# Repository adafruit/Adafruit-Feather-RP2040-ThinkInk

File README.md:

## Adafruit Feather RP2040 ThinkInk with 24-pin E-Paper Display - STEMMA QT PCB

<a href="http://www.adafruit.com/products/5727"><br/>
Click here to purchase one from the Adafruit shop</a>

PCB files for the Adafruit Feather RP2040 ThinkInk with 24-pin E-Paper Display - STEMMA QT. 

Format is EagleCAD schematic and board layout
* https://www.adafruit.com/product/5727

### Description

Easy e-paper and RP2040 finally come to your Feather with this Adafruit RP2040 Feather Think Ink that's designed to make it a breeze to add almost any common e-Ink/e-Paper display. Chances are you've seen one of those new-fangled 'e-readers' like the Kindle or Nook. They have gigantic electronic paper 'static' displays - that means the image stays on the display even when power is completely disconnected. The image is also high contrast and very daylight readable. It really does look just like printed paper!

We've liked these displays for a long time, and we've got Arduino/CircuitPython drivers for tons of the various display chipsets, so wouldn't an e-paper RP2040 Feather make a ton of sense? Luckily for us, just about every small-medium size EInk display made these days has a standard 24-pin connection. This Feather will add all the power supply support circuitry and level shifting so you can attach your favorite display - we've tested it with up to 5.6" sized 7-color ACeP displays.

Since all ePaper displays with the 24-pin interface require you to buffer the layers of data and write them all out at once over SPI, the RP2040 chip is an excellent driver. It has 264K of internal SRAM so even with the largest displays, there's plenty of memory to store all the image data plus run your own code. We also put the display on it's own SPI port so that the Feather's main SPI port can be used for other peripheral devices.

Feather is the development board specification from Adafruit, and like its namesake, it is thin, light, and lets you fly! We designed Feather to be a new standard for portable microcontroller cores. We have other boards in the Feather family, check'em out here.

At the Feather's heart is an RP2040 chip, clocked at 133 MHz and at 3.3V logic, the same one used in the Raspberry Pi Pico. This chip has a whopping MB of onboard QSPI FLASH and 264K of RAM!  There's even room left over for a STEMMA QT connector for plug-and-play of I2C devices.

To make it easy to use for portable projects, we added a connector for any of our 3.7V Lithium polymer batteries and built-in battery charging. You don't need a battery, it will run just fine straight from the USB Type C connector. But, if you do have a battery, you can take it on the go, then plug in the USB to recharge. The Feather will automatically switch over to USB power when it's available. While the RP2040 is not designed for low power usage - you can get down to about 1.5mA of power draw in sleep mode.

Here're some handy specs! You get:

* Measures 2.0" x 0.9" x 0.28" (50.8mm x 22.8mm x 7mm) without headers soldered in
* Light as a (large?) feather - 6.3 grams
* RP2040 32-bit Cortex M0+ dual core running at ~133 MHz @ 3.3V logic and power
* 264 KB RAM
* 8 MB SPI FLASH chip for storing files, images and CircuitPython/MicroPython code storage. No EEPROM
* Tons of GPIO! 21 x GPIO pins with following capabilities:
	* Four 12-bit ADCs (one more than Pico)
	* Two I2C, Two SPI, and two UART peripherals, we label one for the 'main' interface in standard Feather locations
	* 16 x PWM outputs - for servos, LEDs, etc
* Built-in 200mA+ lipoly charger with charging status indicator LED
* Pin #13 red LED for general purpose blinking
* RGB NeoPixel for full-color indication.
* On-board STEMMA QT connector that lets you quickly connect any Qwiic, STEMMA QT or Grove I2C devices with no soldering!
* Both Reset button and Bootloader select button for quick restarts (no unplugging-replugging to relaunch code)
* USB Type C connector lets you access built-in ROM USB bootloader and serial port debugging
* 3.3V regulator with 500mA peak current output and power enable pin
* 4 mounting holes
* 12 MHz crystal for perfect timing.
* Support circuitry for common 24-pin e-Paper/e-Ink displays. These tend to be 1.54" to 7" diagonal and designed for 'smart labels'. No soldering required, simply plug in the display to the FPC connector on the end and load up your code. Not for use with the larger resolution displays on e-Readers like Kindles. Those use a different interface!
Comes assembled and tested, with some header. You'll need a soldering iron to attach the header for installing onto your Feather. Stacking headers will let you put another FeatherWing on top.

Does not come with an EInk display or extension cable! For use with just about any EInk display with a 24-pin FPC connector. See these schematics to verify that your display matches before purchasing.

### License

Adafruit invests time and resources providing this open source design, please support Adafruit and open-source hardware by purchasing products from [Adafruit](https://www.adafruit.com)!

Designed by Limor Fried/Ladyada for Adafruit Industries.

Creative Commons Attribution/Share-Alike, all text above must be included in any redistribution. 
See license.txt for additional details.

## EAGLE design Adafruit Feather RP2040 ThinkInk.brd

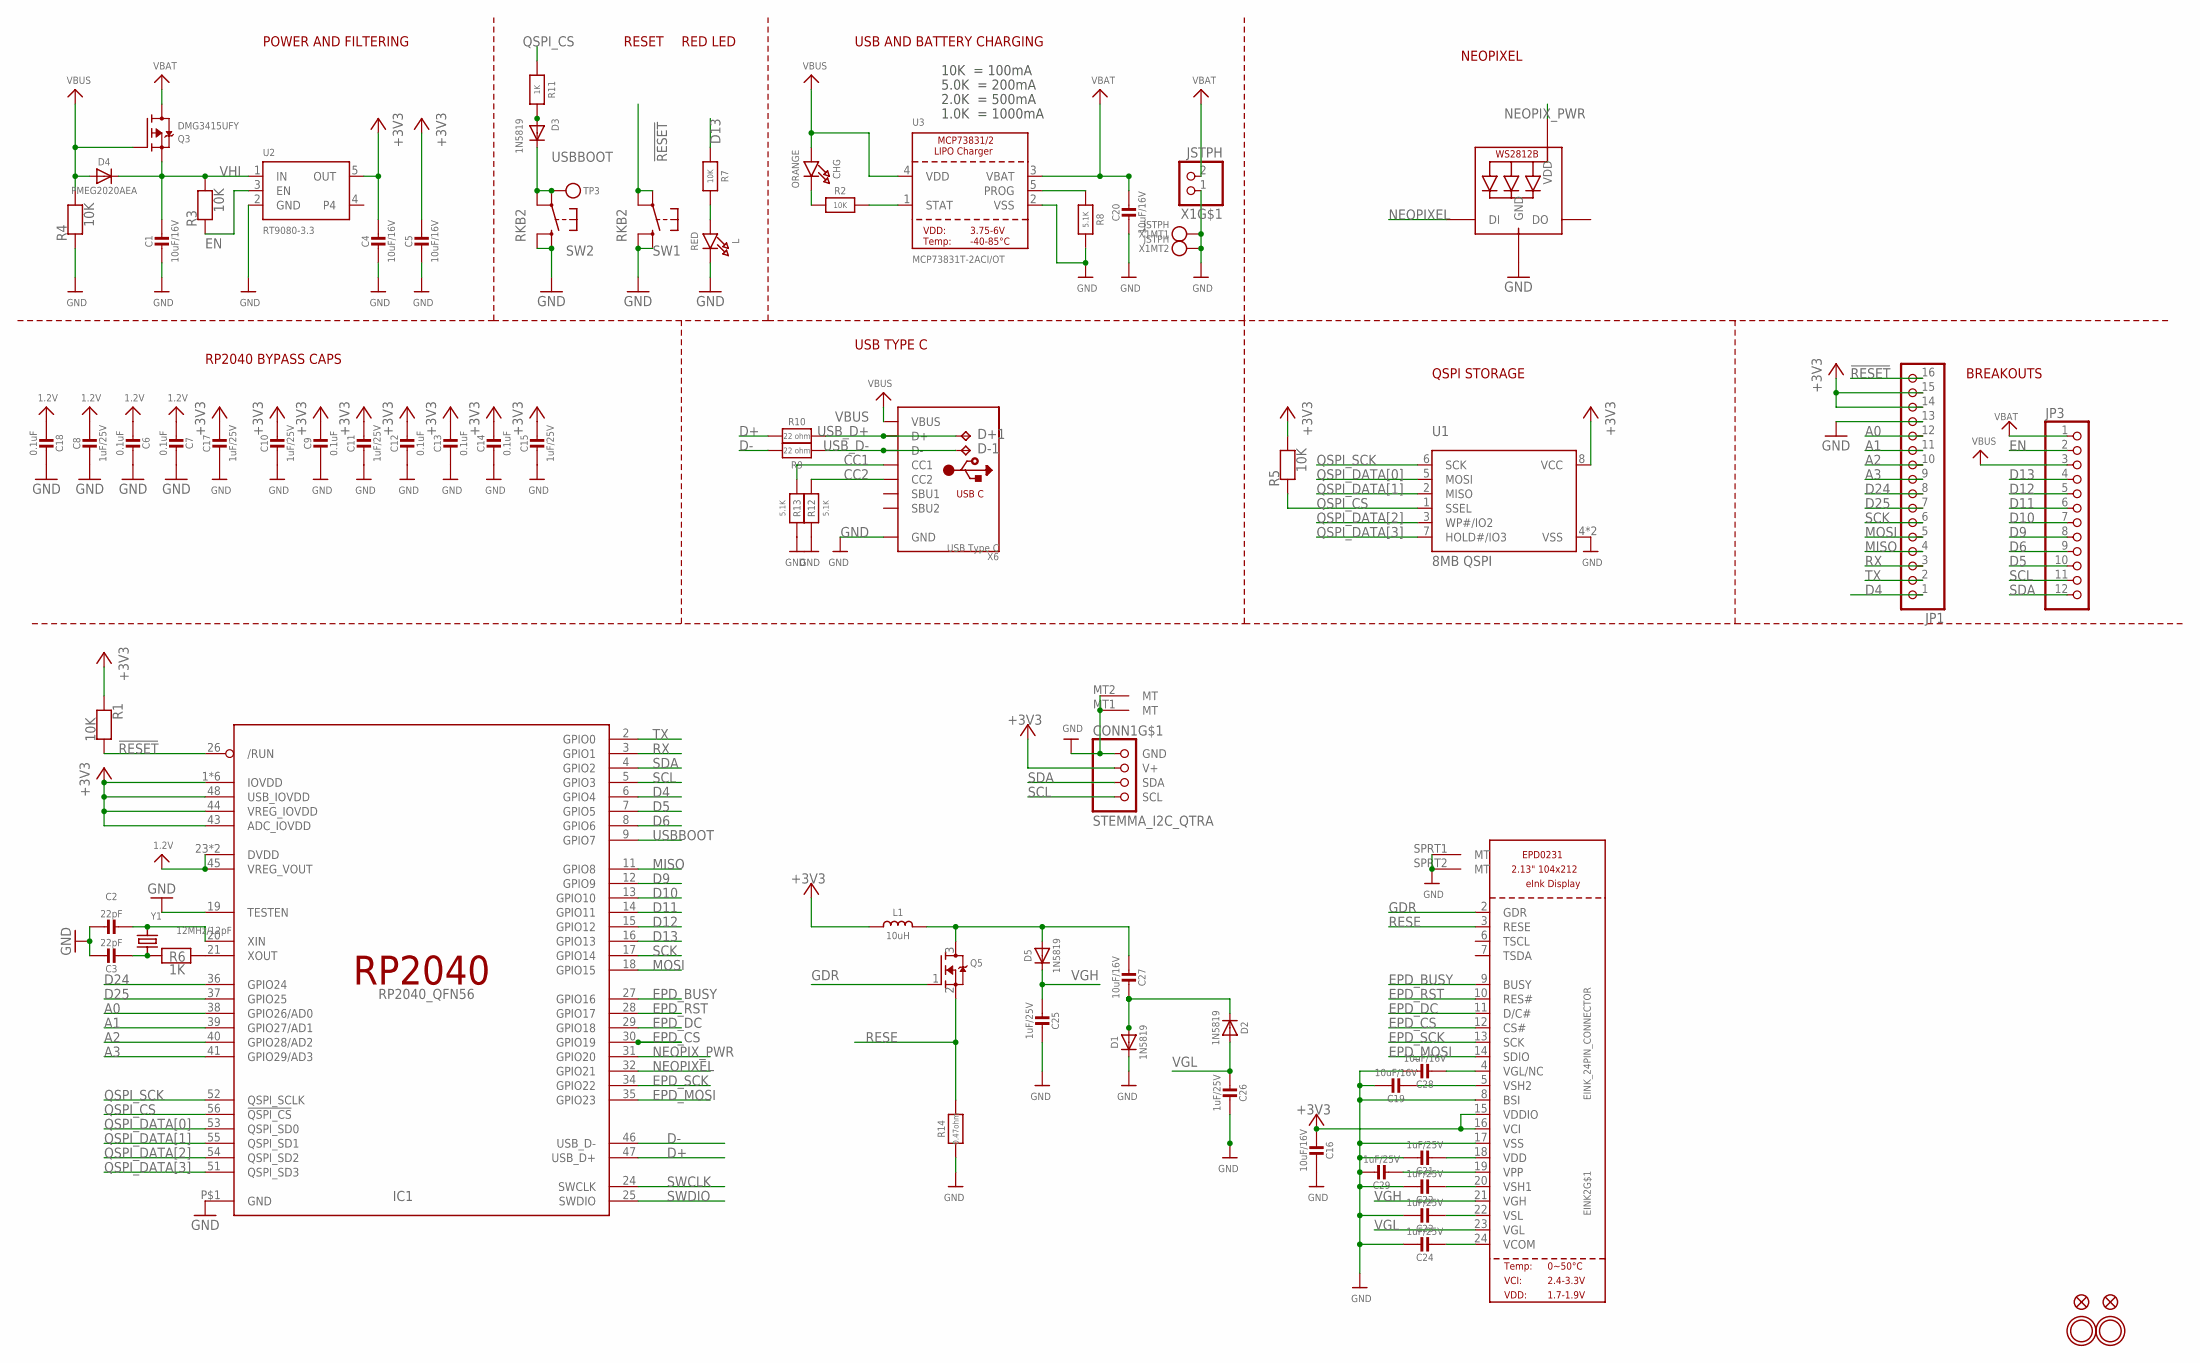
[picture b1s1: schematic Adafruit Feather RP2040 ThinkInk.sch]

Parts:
C1, C4, C5, C16, C19, C20, C27, C28: 10uF/16V; 0805-NO
C2, C3: 22pF; _0402NO
C6, C7, C9, C12, C13, C14, C18: 0.1uF; _0402NO
C8, C10, C11, C15, C17, C21, C22, C23, C24, C25, C26, C29: 1uF/25V; _0402NO
CHG: ORANGE; CHIPLED_0603_NOOUTLINE
CONN1: STEMMA_I2C_QTRA; JST_SH4_RA
D1, D2, D3, D5: 1N5819; SOD-323_MINI
D4: PMEG2020AEA; SOD-323F
D+1: TPB1,27; B1,27
D-1: TPB1,27; B1,27
EINK2: EINK_24PIN_CONNECTOR; EINK_24PIN
IC1: RP2040_QFN56; QFN56_7MM_REDUCEDEPAD
JP1: HEADER-1X16ROUND; 1X16_ROUND
JP3: HEADER-1X12; 1X12_ROUND
L: RED; CHIPLED_0603_NOOUTLINE
L1: 10uH; INDUCTOR_4X4MM_NR401
LED1: WS2812B_SK6805_1515; SK6805_1515
Q3: DMG3415UFY; DFN2015-3
Q5: IRLML0100; SOT23-WIDE
R1, R2, R3, R4, R5, R7: 10K; _0402NO
R6, R11: 1K; _0402NO
R8, R12, R13: 5.1K; _0402NO
R9, R10: 22 ohm; _0402NO
R14: 0.47ohm; 0603-NO
SW1, SW2: RKB2; BTN_RKB2_4.6X2.8
TP3: TESTPOINTROUND1.5MMNO; TESTPOINT_ROUND_1.5MM_NO
U1: 8MB QSPI; USON8_4X4
U2: RT9080-3.3; SOT23-5; JLC_ROTATION 0
U3: MCP73831T-2ACI/OT; SOT23-5
U$31, U$32: MOUNTINGHOLE2.5; MOUNTINGHOLE_2.5_PLATED
U$34, U$35: FIDUCIAL_1MM
X1: JSTPH; JSTPH2_BATT
X6: USB Type C; USB_C_CUSB31-CFM2AX-01-X
Y1: 12MHz/12pF; CRYSTAL_2.5X2

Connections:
1.2V: C6.2, C7.2, C8.1, C18.2, IC1.23 (DVDD), IC1.45 (VREG_VOUT), IC1.50 (DVDD)
!RESET: IC1.26 (/RUN), JP1.16, R1.2, SW1.A, SW1.A' (P1)
+3V3: C4.1, C5.1, C9.1, C10.1, C11.1, C12.1, C13.1, C14.1, C15.1, C16.2, C17.1, CONN1.2 (V+), EINK2.15 (VDDIO), EINK2.16 (VCI), IC1.1 (IOVDD), IC1.10 (IOVDD), IC1.22 (IOVDD), IC1.33 (IOVDD), IC1.42 (IOVDD), IC1.43 (ADC_IOVDD), IC1.44 (VREG_IOVDD), IC1.48 (USB_IOVDD), IC1.49 (IOVDD), JP1.14, JP1.15, L1.P$2 (2), R1.1, R5.2, U1.8 (VCC), U2.5 (OUT)
A0: IC1.38 (GPIO26/AD0), JP1.12
A1: IC1.39 (GPIO27/AD1), JP1.11
A2: IC1.40 (GPIO28/AD2), JP1.10
A3: IC1.41 (GPIO29/AD3), JP1.9
CC1: R13.2, X6.A5 (CC1)
CC2: R12.2, X6.B5 (CC2)
D4: IC1.6 (GPIO4), JP1.1
D5: IC1.7 (GPIO5), JP3.10
D6: IC1.8 (GPIO6), JP3.9
D9: IC1.12 (GPIO9), JP3.8
D10: IC1.13 (GPIO10), JP3.7
D11: IC1.14 (GPIO11), JP3.6
D12: IC1.15 (GPIO12), JP3.5
D13: IC1.16 (GPIO13), JP3.4, R7.1
D24: IC1.36 (GPIO24), JP1.8
D25: IC1.37 (GPIO25), JP1.7
D+: IC1.47 (USB_D+), R10.2
D-: IC1.46 (USB_D-), R9.2
EN: JP3.2, R3.1, U2.3 (EN)
EPD_BUSY: EINK2.9 (BUSY), IC1.27 (GPIO16)
EPD_CS: EINK2.12 (CS#), IC1.30 (GPIO19)
EPD_DC: EINK2.11 (D/C#), IC1.29 (GPIO18)
EPD_MOSI: EINK2.14 (SDIO), IC1.35 (GPIO23)
EPD_RST: EINK2.10 (RES#), IC1.28 (GPIO17)
EPD_SCK: EINK2.13 (SCK), IC1.34 (GPIO22)
GDR: EINK2.2 (GDR), Q5.1 (G)
GND: C1.2, C2.1, C3.1, C4.2, C5.2, C6.1, C7.1, C8.2, C9.2, C10.2, C11.2, C12.2, C13.2, C14.2, C15.2, C16.1, C17.2, C18.1, C19.1, C20.2, C21.1, C22.1, C23.1, C24.1, C25.2, C26.2, C28.1, C29.1, CONN1.1 (GND), CONN1.MT1 (MT), CONN1.MT2 (MT), D1.C, EINK2.8 (BSI), EINK2.17 (VSS), EINK2.SPRT1 (MT), EINK2.SPRT2 (MT), IC1.19 (TESTEN), IC1.P$1 (GND), JP1.13, L.C, LED1.4 (GND), R4.1, R8.2, R12.1, R13.1, R14.2, SW1.B (S), SW1.B' (S1), SW2.B (S), SW2.B' (S1), U1.4 (VSS), U1.PAD (VSS), U2.2 (GND), U3.2 (VSS), X1.1, X1.NC1, X1.NC2, X6.A1B12 (GND), X6.B1A12 (GND)
MISO: IC1.11 (GPIO8), JP1.4
MOSI: IC1.18 (GPIO15), JP1.5
unnamed: CHG.C, R2.1
unnamed: L.A, R7.2
unnamed: R2.2, U3.1 (STAT)
unnamed: R8.1, U3.5 (PROG)
unnamed: C2.2, IC1.20 (XIN), Y1.3 (2)
unnamed: C3.2, R6.1, Y1.1
unnamed: IC1.21 (XOUT), R6.2
unnamed: C19.2, EINK2.5 (VSH2)
unnamed: C21.2, EINK2.18 (VDD)
unnamed: C22.2, EINK2.20 (VSH1)
unnamed: C27.2, D1.A, D2.C
unnamed: C27.1, D5.A, L1.P$1 (1), Q5.3 (D)
unnamed: C28.2, EINK2.4 (VGL/NC)
unnamed: C29.2, EINK2.19 (VPP)
unnamed: D3.A, R11.2
unnamed: C23.2, EINK2.22 (VSL)
unnamed: C24.2, EINK2.24 (VCOM)
NEOPIXEL: IC1.32 (GPIO21), LED1.1 (DI)
NEOPIX_PWR: IC1.31 (GPIO20), LED1.2 (VDD)
QSPI_CS: IC1.56 (!QSPI_CS), R5.1, R11.1, U1.1 (SSEL)
QSPI_DATA[0]: IC1.53 (QSPI_SD0), U1.5 (MOSI)
QSPI_DATA[1]: IC1.55 (QSPI_SD1), U1.2 (MISO)
QSPI_DATA[2]: IC1.54 (QSPI_SD2), U1.3 (WP#/IO2)
QSPI_DATA[3]: IC1.51 (QSPI_SD3), U1.7 (HOLD#/IO3)
QSPI_SCK: IC1.52 (QSPI_SCLK), U1.6 (SCK)
RESE: EINK2.3 (RESE), Q5.2 (S), R14.1
RX: IC1.3 (GPIO1), JP1.3
SCK: IC1.17 (GPIO14), JP1.6
SCL: CONN1.4 (SCL), IC1.5 (GPIO3), JP3.11
SDA: CONN1.3 (SDA), IC1.4 (GPIO2), JP3.12
SWCLK: IC1.24 (SWCLK)
SWDIO: IC1.25 (SWDIO)
TX: IC1.2 (GPIO0), JP1.2
USBBOOT: D3.C, IC1.9 (GPIO7), SW2.A, SW2.A' (P1), TP3.P$1
USB_D+: D+1.TP, R10.1, X6.A6 (D+), X6.B6 (D+)
USB_D-: D-1.TP, R9.1, X6.A7 (D-), X6.B7 (D-)
VBAT: C20.1, JP3.1, Q3.3 (D), U3.3 (VBAT), X1.2
VBUS: CHG.A, D4.A, JP3.3, Q3.1 (G), R4.2, U3.4 (VDD), X6.A4B9 (VBUS), X6.B4A9 (VBUS)
VGH: C25.1, D5.C, EINK2.21 (VGH)
VGL: C26.1, D2.A, EINK2.23 (VGL)
VHI: C1.1, D4.C, Q3.2 (S), R3.2, U2.1 (IN)

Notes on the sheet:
POWER AND FILTERING
RESET
10K = 100mA
5.0K = 200mA
2.0K = 500mA
1.0K = 1000mA
USB AND BATTERY CHARGING
BREAKOUTS
RED LED
RP2040 BYPASS CAPS
USB TYPE C
QSPI STORAGE
NEOPIXEL

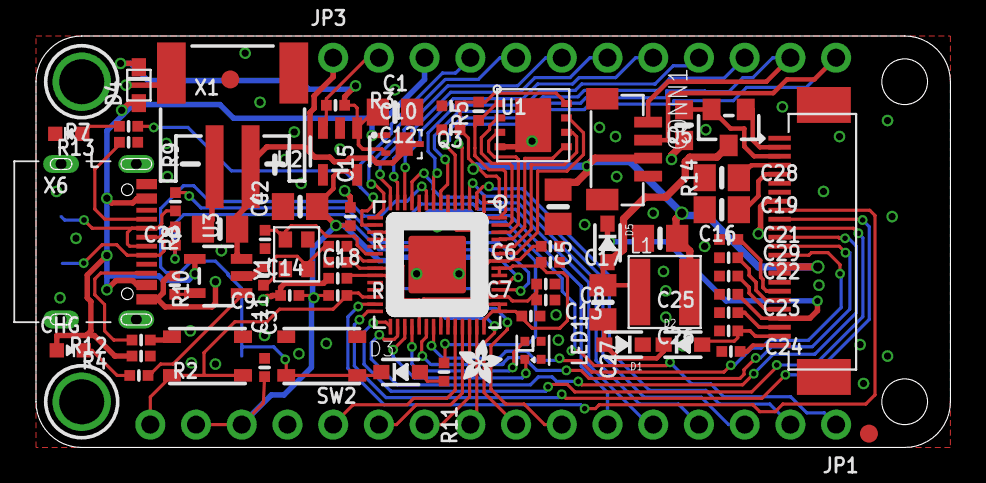
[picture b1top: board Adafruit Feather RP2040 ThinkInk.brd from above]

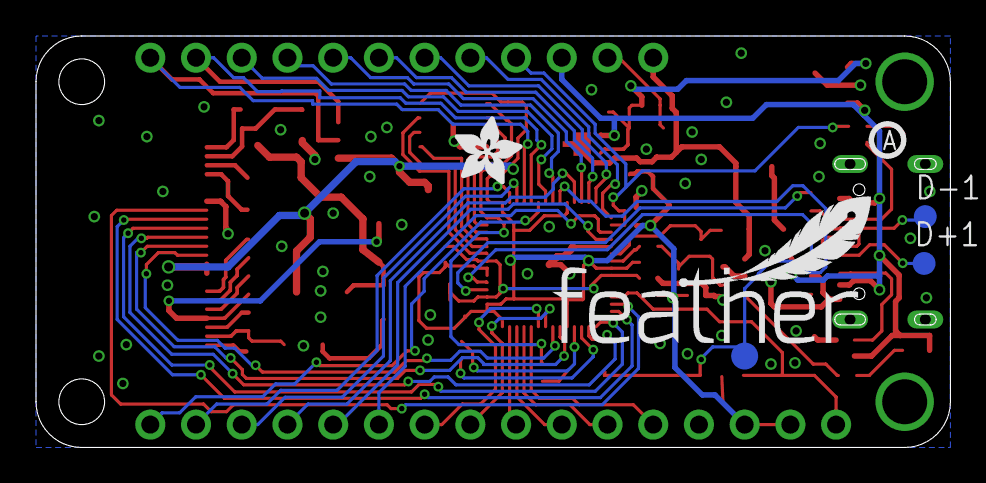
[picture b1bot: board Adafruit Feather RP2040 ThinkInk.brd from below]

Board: 2 copper layers, 50.8 x 22.9 mm, 145 parts (38 on the bottom side), 71 nets.

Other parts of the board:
PLABEL0: PLABEL0
PLABEL1: PLABEL1
PLABEL2: PLABEL2
PLABEL3: PLABEL3
PLABEL4: PLABEL4
PLABEL5: PLABEL5
PLABEL6: PLABEL6
PLABEL7: PLABEL7
PLABEL8: PLABEL8
PLABEL9: PLABEL9
PLABEL10: PLABEL10
PLABEL11: PLABEL11
PLABEL12: PLABEL12
PLABEL13: PLABEL13
PLABEL14: PLABEL14
PLABEL15: PLABEL15
PLABEL16: PLABEL16
PLABEL17: PLABEL17
PLABEL18: PLABEL18
PLABEL19: PLABEL19
PLABEL20: PLABEL20
PLABEL21: PLABEL21
PLABEL22: PLABEL22
PLABEL23: PLABEL23
PLABEL24: PLABEL24
PLABEL25: PLABEL25
PLABEL26: PLABEL26
PLABEL27: PLABEL27
PLABEL28: PLABEL28
PLABEL29: PLABEL29
PLABEL30: PLABEL30
PLABEL31: PLABEL31
PLABEL32: PLABEL32
PLABEL33: PLABEL33
PLABEL34: PLABEL34
PLABEL35: PLABEL35
PLABEL36: PLABEL36
PLABEL37: PLABEL37
PLABEL38: PLABEL38
PLABEL39: PLABEL39
PLABEL40: PLABEL40
PLABEL41: PLABEL41
PLABEL42: PLABEL42
PLABEL43: PLABEL43
PLABEL44: PLABEL44
PLABEL45: PLABEL45
PLABEL46: PLABEL46
PLABEL47: PLABEL47
PLABEL48: PLABEL48
PLABEL49: PLABEL49
PLABEL50: PLABEL50
PLABEL51: PLABEL51
PLABEL52: PLABEL52
PLABEL53: PLABEL53
PLABEL54: PLABEL54
PLABEL55: PLABEL55
PLABEL56: PLABEL56
PLABEL57: PLABEL57
PLABEL58: PLABEL58
PLABEL59: PLABEL59
PLABEL60: PLABEL60
PLABEL61: PLABEL61
PLABEL62: PLABEL62
PLABEL63: PLABEL63
PLABEL64: PLABEL64
PLABEL65: PLABEL65
PLABEL66: PLABEL66
U$13: PCBFEAT-REV-040
U$28: ADAFRUIT_2.5MM
U$42: ADAFRUIT_3.5MM
U$46: FEATHERLOGO_MED

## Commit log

2023-05-01 Adding cookiecutter output
2023-05-01 adding factory reset
2023-05-01 updating prettypins
2025-09-24 Update battery connector image

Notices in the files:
parts and their libraries:
microbuilder: This work is placed in the public domain, and may be freely used for commercial and non-commercial work with the following conditions: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
